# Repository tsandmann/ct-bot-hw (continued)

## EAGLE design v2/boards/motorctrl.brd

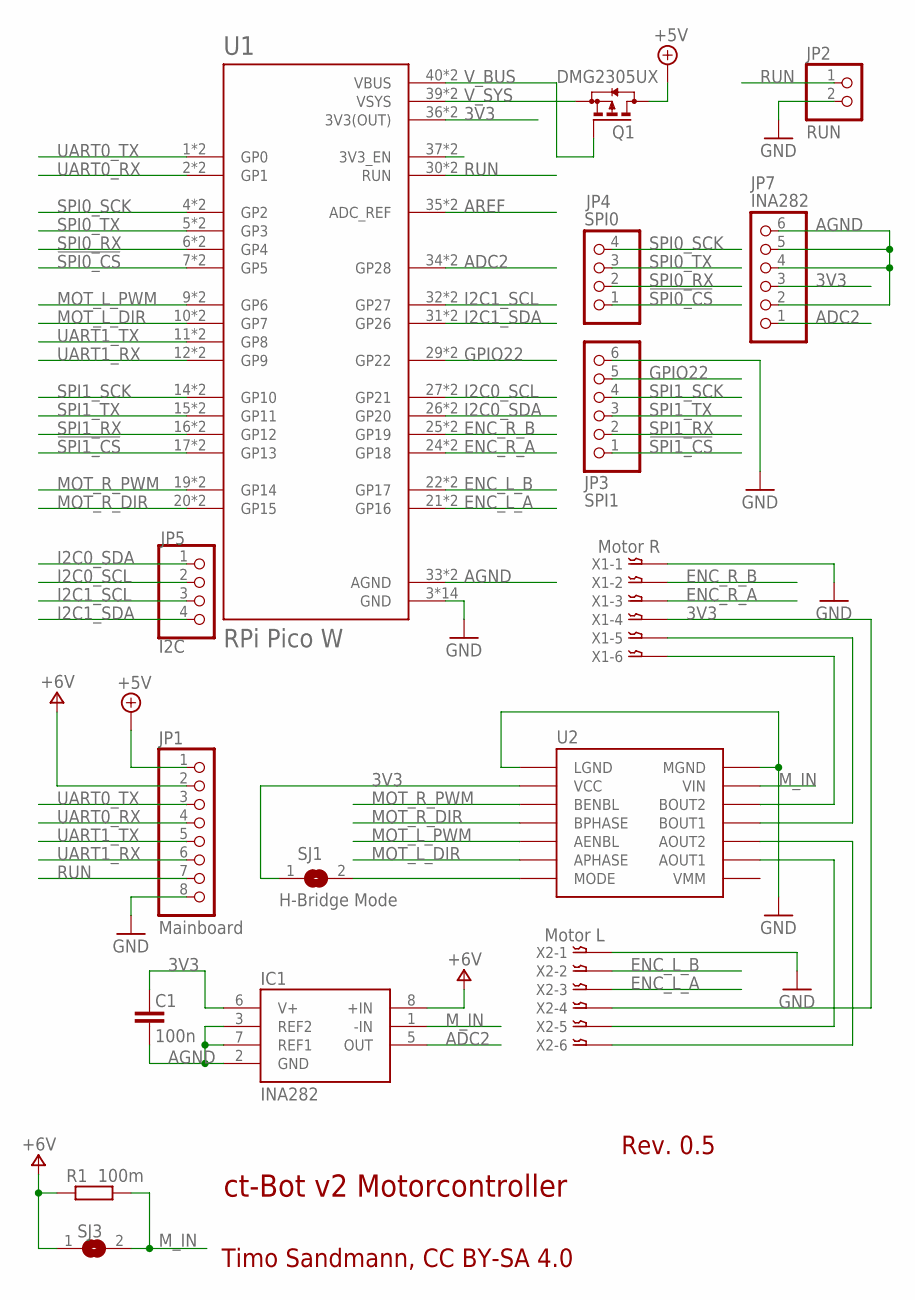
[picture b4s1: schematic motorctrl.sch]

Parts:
C1: 100n; C0805
IC1: INA282; SO08
JP1: Mainboard; 1X08
JP2: RUN; 1X02
JP3: SPI1; 1X06
JP4: SPI0; 1X04
JP5: I2C; 1X04
JP7: INA282; 1X06
Q1: DMG2305UX; SOT23
R1: 100m; R2512
SJ1: H-Bridge Mode; SJ
SJ3: VREF; SJ
U1: RPi Pico W; PICO-PKG-NO_DEBUG
U2: DRV8835THROUGHHOLE; DRV8835
X1: Motor R; B6B-XH
X2: Motor L; B6B-XH

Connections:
3V3: C1.2, IC1.6 (V+), JP7.3, SJ1.1, U1.36 (3V3(OUT)), U1.P$36 (3V3(OUT)), U2.VCC, X1.P$4, X2.P$4
3V3_EN: U1.37 (3V3_EN), U1.P$37 (3V3_EN)
!SPI0_CS: JP4.1, U1.7 (GP5), U1.P$7 (GP5)
!SPI1_CS: JP3.1, U1.17 (GP13), U1.P$17 (GP13)
+5V: JP1.1, Q1.3 (D)
+6V: IC1.8 (+IN), JP1.2, R1.1, SJ3.1
ADC2: IC1.5 (OUT), JP7.1, U1.34 (GP28), U1.P$34 (GP28)
AGND: C1.1, IC1.2 (GND), IC1.3 (REF2), IC1.7 (REF1), JP7.2, JP7.4, JP7.5, JP7.6, U1.33 (AGND), U1.P$33 (AGND)
AREF: U1.35 (ADC_REF), U1.P$35 (ADC_REF)
ENC_L_A: U1.21 (GP16), U1.P$21 (GP16), X2.P$3
ENC_L_B: U1.22 (GP17), U1.P$22 (GP17), X2.P$2
ENC_R_A: U1.24 (GP18), U1.P$24 (GP18), X1.P$3
ENC_R_B: U1.25 (GP19), U1.P$25 (GP19), X1.P$2
GND: JP1.8, JP2.2, JP3.6, U1.3 (GND), U1.8 (GND), U1.13 (GND), U1.18 (GND), U1.23 (GND), U1.28 (GND), U1.38 (GND), U1.P$3 (GND), U1.P$8 (GND), U1.P$13 (GND), U1.P$18 (GND), U1.P$23 (GND), U1.P$28 (GND), U1.P$38 (GND), U2.LGND, U2.MGND, X1.P$1, X2.P$1
GPIO22: JP3.5, U1.29 (GP22), U1.P$29 (GP22)
I2C0_SCL: JP5.2, U1.27 (GP21), U1.P$27 (GP21)
I2C0_SDA: JP5.1, U1.26 (GP20), U1.P$26 (GP20)
I2C1_SCL: JP5.3, U1.32 (GP27), U1.P$32 (GP27)
I2C1_SDA: JP5.4, U1.31 (GP26), U1.P$31 (GP26)
MOT_L_DIR: U1.10 (GP7), U1.P$10 (GP7), U2.APHASE
MOT_L_PWM: U1.9 (GP6), U1.P$9 (GP6), U2.AENBL
MOT_R_DIR: U1.20 (GP15), U1.P$20 (GP15), U2.BPHASE
MOT_R_PWM: U1.19 (GP14), U1.P$19 (GP14), U2.BENBL
M_IN: IC1.1 (-IN), R1.2, SJ3.2, U2.VIN
unnamed: SJ1.2, U2.MODE
unnamed: U2.BOUT1, X1.P$5
unnamed: U2.BOUT2, X1.P$6
unnamed: U2.AOUT1, X2.P$5
unnamed: U2.AOUT2, X2.P$6
RUN: JP1.7, JP2.1, U1.30 (RUN), U1.P$30 (RUN)
SPI0_RX: JP4.2, U1.6 (GP4), U1.P$6 (GP4)
SPI0_SCK: JP4.4, U1.4 (GP2), U1.P$4 (GP2)
SPI0_TX: JP4.3, U1.5 (GP3), U1.P$5 (GP3)
SPI1_RX: JP3.2, U1.16 (GP12), U1.P$16 (GP12)
SPI1_SCK: JP3.4, U1.14 (GP10), U1.P$14 (GP10)
SPI1_TX: JP3.3, U1.15 (GP11), U1.P$15 (GP11)
UART0_RX: JP1.4, U1.2 (GP1), U1.P$2 (GP1)
UART0_TX: JP1.3, U1.1 (GP0), U1.P$1 (GP0)
UART1_RX: JP1.6, U1.12 (GP9), U1.P$12 (GP9)
UART1_TX: JP1.5, U1.11 (GP8), U1.P$11 (GP8)
V_BUS: Q1.1 (G), U1.40 (VBUS), U1.P$40 (VBUS)
V_SYS: Q1.2 (S), U1.39 (VSYS), U1.P$39 (VSYS)

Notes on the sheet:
Rev. 0.5
Timo Sandmann, CC BY-SA 4.0
ct-Bot v2 Motorcontroller

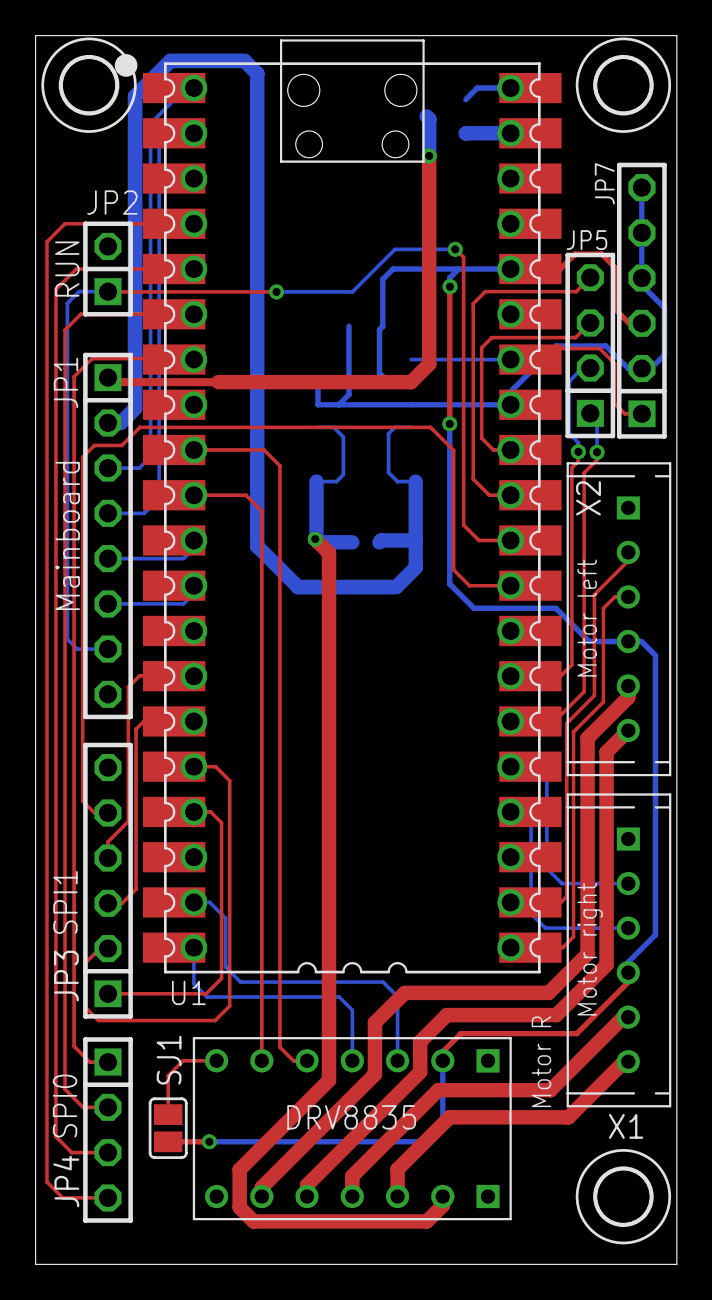
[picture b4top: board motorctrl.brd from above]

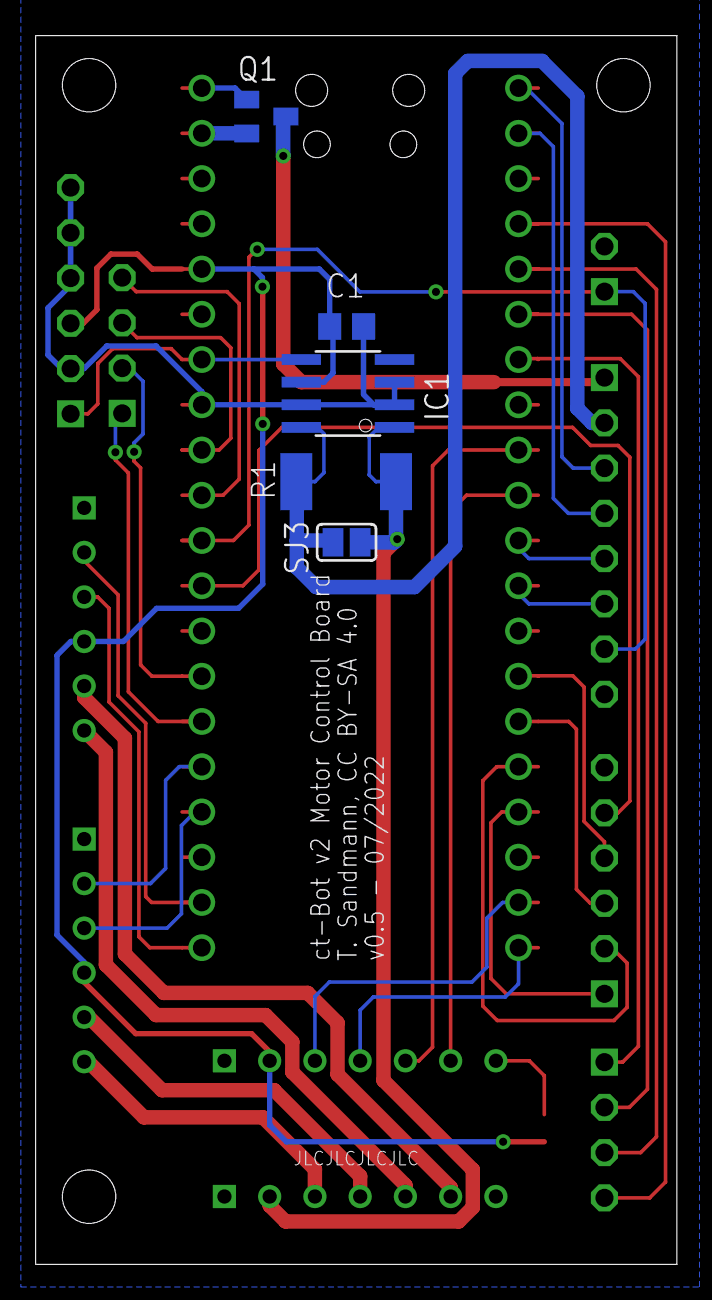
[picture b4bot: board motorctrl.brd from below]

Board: 2 copper layers, 36.0 x 69.0 mm, 19 parts (5 on the bottom side), 42 nets.

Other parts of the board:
H1, H2, H3: MOUNT-HOLE3.0; 3,0

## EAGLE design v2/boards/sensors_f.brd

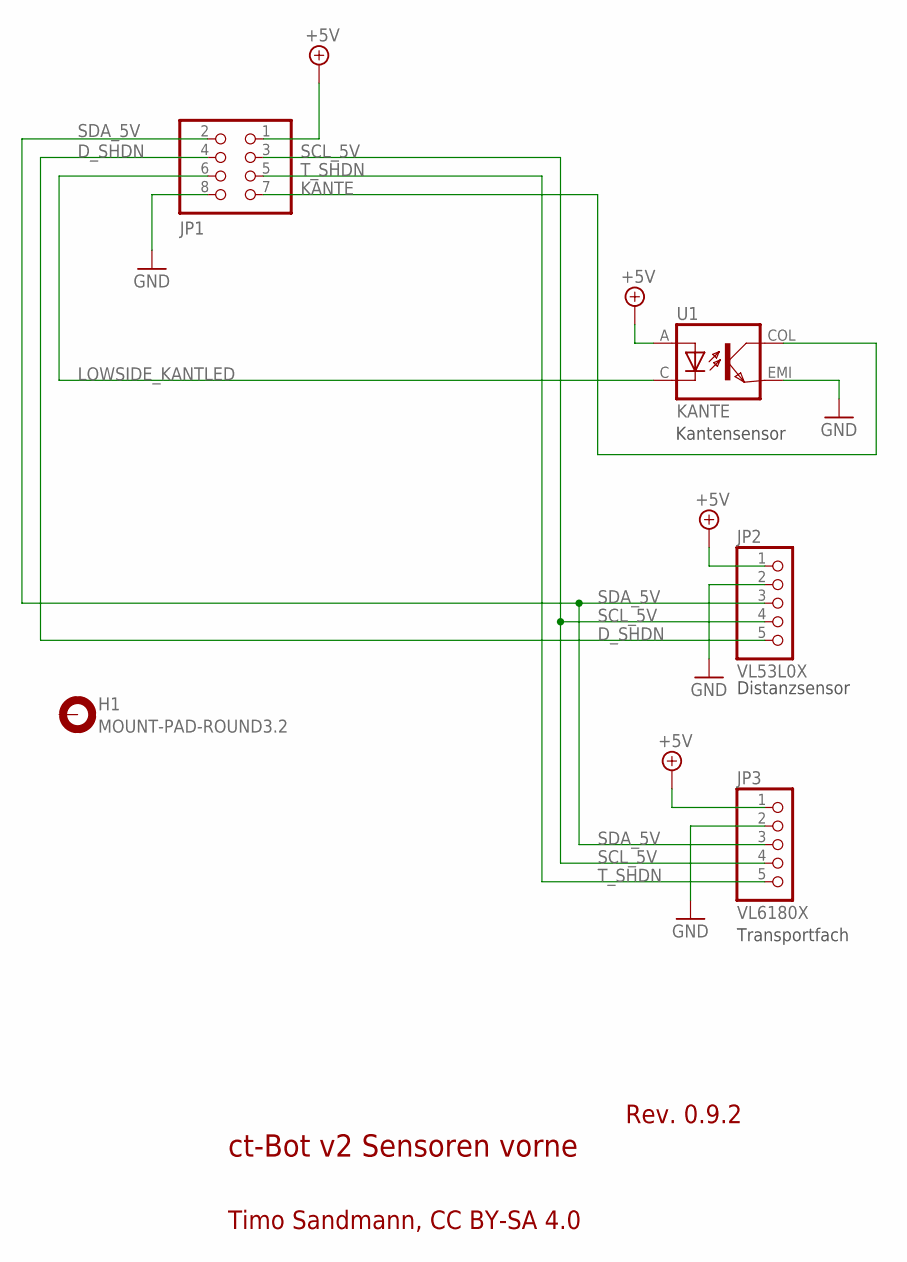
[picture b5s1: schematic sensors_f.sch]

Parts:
H1: MOUNT-PAD-ROUND3.2; 3,2-PAD
JP1: PINHD-2X4; 2X04
JP2: VL53L0X; 1X05
JP3: VL6180X; 1X05
U1: KANTE; EDGE

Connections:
+5V: JP1.1, JP2.1, JP3.1, U1.A
D_SHDN: JP1.4, JP2.5
GND: JP1.8, JP2.2, JP3.2, U1.EMI
KANTE: JP1.7, U1.COL
LOWSIDE_KANTLED: JP1.6, U1.C
SCL_5V: JP1.3, JP2.4, JP3.4
SDA_5V: JP1.2, JP2.3, JP3.3
T_SHDN: JP1.5, JP3.5

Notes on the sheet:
ct-Bot v2 Sensoren vorne
Rev. 0.9.2
Timo Sandmann, CC BY-SA 4.0
Kantensensor
Distanzsensor
Transportfach

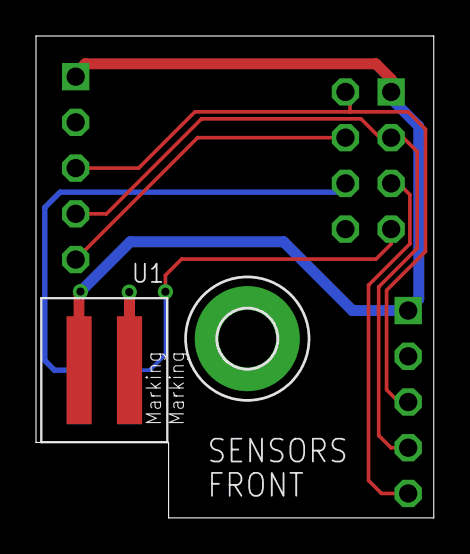
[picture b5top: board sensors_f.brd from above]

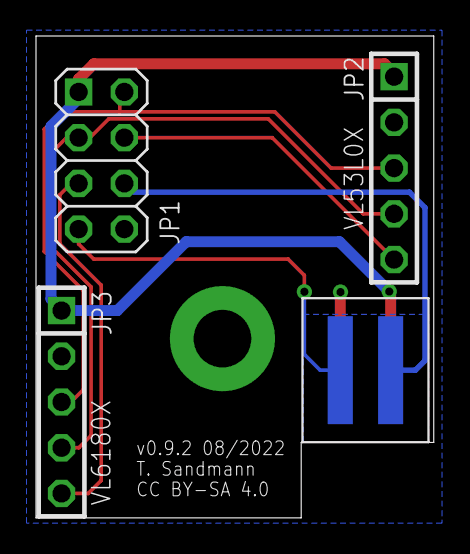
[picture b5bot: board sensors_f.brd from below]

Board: 2 copper layers, 22.1 x 26.8 mm, 5 parts (3 on the bottom side), 8 nets.

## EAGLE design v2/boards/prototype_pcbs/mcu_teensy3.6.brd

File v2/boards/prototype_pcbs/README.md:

# ct-Bot v2 prototype test boards

These boards (a simplified mainboard, a teensy mcu board, and three sensor boards) are ***prototypes*** just for ***development and testing***. They are provided "as is" without warranty of any kind.

## Simplified mainboard

To achieve a more cost-effective prototype board with only two layers, some optional extensions have been omitted, and the various I2C buses have been combined. See [mainboard_2l_0.8.3.pdf](mainboard_2l_0.8.3.pdf) for the simplified schematic. However, the basic functionality has been successfully tested. See [known issues](#Known-issues-and-notes) for problems discovered so far.

## Known issues and notes

Please note: these problem lists may be highly incomplete, as not all functions have been tested yet!

### [Mainboard](mainboard_2l_0.8.3.pdf)

* *I2C0* Pullups may be incorrect, depending on the connected modules, line capacities are not considered.
* A pullup is missing on ESP32's RX line.
* Reset buttons for MCU and ESP32 are missing.
* Analog signal paths are noisy due to simplified 2-layer design.
* There may be crosstalk due to the simplified 2-layer design.
* The BNO055 sensor connector should be extended by another one for an MPU 6050 sensor (as a better alternative).

### [Teensy MCU board](mcu_teensy_0.8.4.pdf)

* 3V3 reference voltage should be added to increase accurancy and stability of ADC.
* *I2C0_5V* is not necessary.
* *U2* and *Q1* are not necessary.
* RTC bat is not necessary.

### [Line sensor board (bottom)](sensors_b_0.8.4.pdf)

* Signals for left and right line sensors are swapped. Workaround: exchange *LINE_L* and *LINE_R* on mainboard connector or swap pin mappings in software.

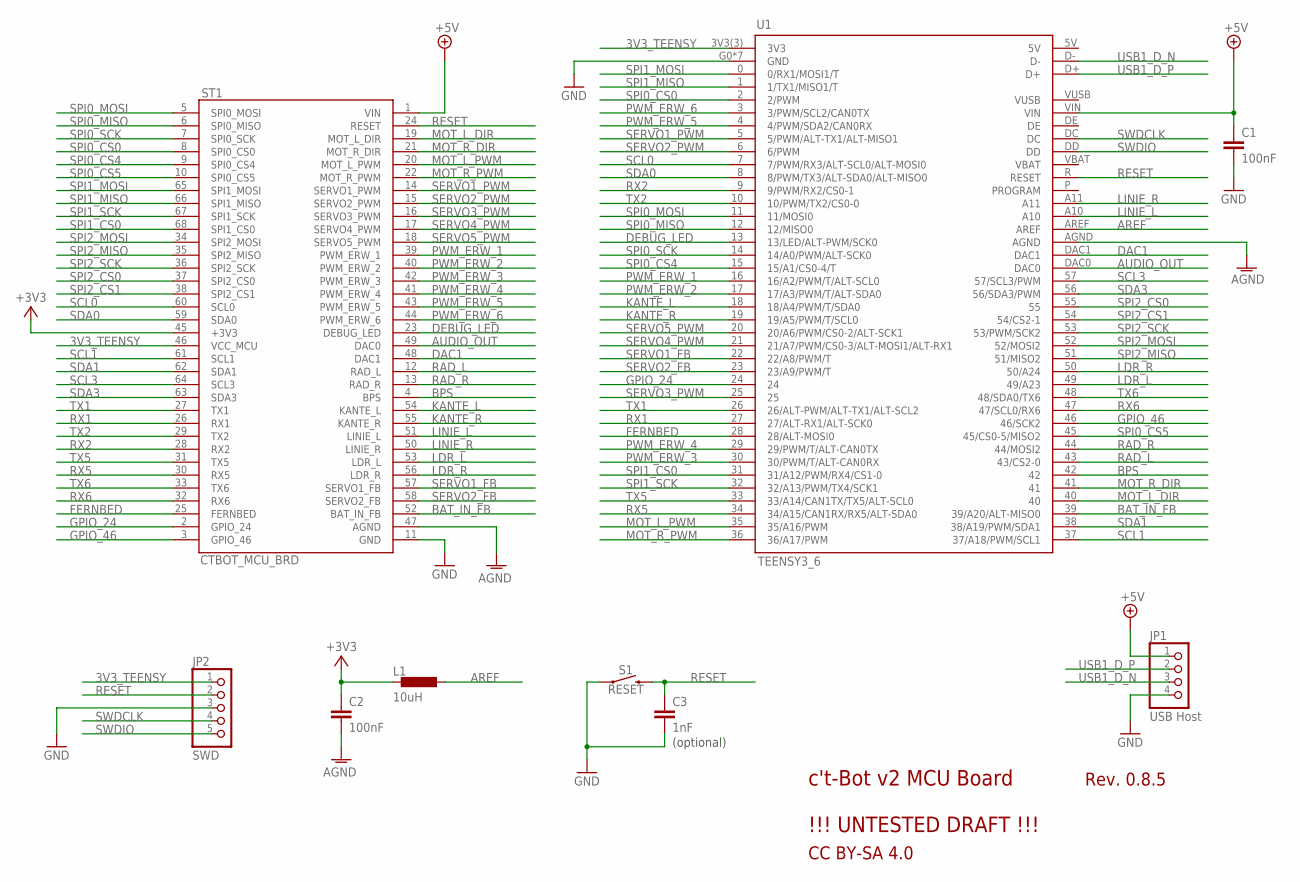
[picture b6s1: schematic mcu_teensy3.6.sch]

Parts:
C1, C2: 100nF; C025-025X050
C3: 1nF; C025-025X050
JP1: USB Host; 1X04/90
JP2: SWD; 1X05/90
L1: 10uH; 0207/10
S1: RESET; TACTILE_SWITCH_PTH_6.0MM
ST1: CTBOT_MCU_BRD; DIP66
U1: TEENSY3_6; T36

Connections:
3V3_TEENSY: JP2.1, ST1.46 (VCC_MCU), U1.3V3(3) (3V3)
+3V3: C2.1, L1.2, ST1.45 (+3V3)
+5V: C1.1, JP1.1, ST1.1 (VIN), U1.VIN
AGND: C2.2, ST1.47 (AGND), U1.AGND
AREF: L1.1, U1.AREF
AUDIO_OUT: ST1.49 (DAC0), U1.DAC0
BAT_IN_FB: ST1.52 (BAT_IN_FB), U1.39 (39/A20/ALT-MISO0)
BPS: ST1.4 (BPS), U1.42
DAC1: ST1.48 (DAC1), U1.DAC1
DEBUG_LED: ST1.23 (DEBUG_LED), U1.13 (13/LED/ALT-PWM/SCK0)
FERNBED: ST1.25 (FERNBED), U1.28 (28/ALT-MOSI0)
GND: C1.2, C3.2, JP1.4, JP2.3, S1.1, ST1.11 (GND), U1.G0 (GND), U1.G1 (GND), U1.G2 (GND), U1.G3 (GND), U1.G4 (GND), U1.G5 (GND), U1.G6 (GND)
GPIO_24: ST1.2 (GPIO_24), U1.24
GPIO_46: ST1.3 (GPIO_46), U1.46 (46/SCK2)
KANTE_L: ST1.54 (KANTE_L), U1.18 (18/A4/PWM/T/SDA0)
KANTE_R: ST1.55 (KANTE_R), U1.19 (19/A5/PWM/T/SCL0)
LDR_L: ST1.53 (LDR_L), U1.49 (49/A23)
LDR_R: ST1.56 (LDR_R), U1.50 (50/A24)
LINIE_L: ST1.51 (LINIE_L), U1.A10
LINIE_R: ST1.50 (LINIE_R), U1.A11
MOT_L_DIR: ST1.19 (MOT_L_DIR), U1.40
MOT_L_PWM: ST1.20 (MOT_L_PWM), U1.35 (35/A16/PWM)
MOT_R_DIR: ST1.21 (MOT_R_DIR), U1.41
MOT_R_PWM: ST1.22 (MOT_R_PWM), U1.36 (36/A17/PWM)
PWM_ERW_1: ST1.39 (PWM_ERW_1), U1.16 (16/A2/PWM/T/ALT-SCL0)
PWM_ERW_2: ST1.40 (PWM_ERW_2), U1.17 (17/A3/PWM/T/ALT-SDA0)
PWM_ERW_3: ST1.42 (PWM_ERW_3), U1.30 (30/PWM/T/ALT-CAN0RX)
PWM_ERW_4: ST1.41 (PWM_ERW_4), U1.29 (29/PWM/T/ALT-CAN0TX)
PWM_ERW_5: ST1.43 (PWM_ERW_5), U1.4 (4/PWM/SDA2/CAN0RX)
PWM_ERW_6: ST1.44 (PWM_ERW_6), U1.3 (3/PWM/SCL2/CAN0TX)
RAD_L: ST1.12 (RAD_L), U1.43 (43/CS2-0)
RAD_R: ST1.13 (RAD_R), U1.44 (44/MOSI2)
RESET: C3.1, JP2.2, S1.3 (2), ST1.24 (RESET), U1.R (RESET)
RX1: ST1.26 (RX1), U1.27 (27/ALT-RX1/ALT-SCK0)
RX2: ST1.28 (RX2), U1.9 (9/PWM/RX2/CS0-1)
RX5: ST1.30 (RX5), U1.34 (34/A15/CAN1RX/RX5/ALT-SDA0)
RX6: ST1.32 (RX6), U1.47 (47/SCL0/RX6)
SCL0: ST1.60 (SCL0), U1.7 (7/PWM/RX3/ALT-SCL0/ALT-MOSI0)
SCL1: ST1.61 (SCL1), U1.37 (37/A18/PWM/SCL1)
SCL3: ST1.64 (SCL3), U1.57 (57/SCL3/PWM)
SDA0: ST1.59 (SDA0), U1.8 (8/PWM/TX3/ALT-SDA0/ALT-MISO0)
SDA1: ST1.62 (SDA1), U1.38 (38/A19/PWM/SDA1)
SDA3: ST1.63 (SDA3), U1.56 (56/SDA3/PWM)
SERVO1_FB: ST1.57 (SERVO1_FB), U1.22 (22/A8/PWM/T)
SERVO1_PWM: ST1.14 (SERVO1_PWM), U1.5 (5/PWM/ALT-TX1/ALT-MISO1)
SERVO2_FB: ST1.58 (SERVO2_FB), U1.23 (23/A9/PWM/T)
SERVO2_PWM: ST1.15 (SERVO2_PWM), U1.6 (6/PWM)
SERVO3_PWM: ST1.16 (SERVO3_PWM), U1.25
SERVO4_PWM: ST1.17 (SERVO4_PWM), U1.21 (21/A7/PWM/CS0-3/ALT-MOSI1/ALT-RX1)
SERVO5_PWM: ST1.18 (SERVO5_PWM), U1.20 (20/A6/PWM/CS0-2/ALT-SCK1)
SPI0_CS0: ST1.8 (SPI0_CS0), U1.2 (2/PWM)
SPI0_CS4: ST1.9 (SPI0_CS4), U1.15 (15/A1/CS0-4/T)
SPI0_CS5: ST1.10 (SPI0_CS5), U1.45 (45/CS0-5/MISO2)
SPI0_MISO: ST1.6 (SPI0_MISO), U1.12 (12/MISO0)
SPI0_MOSI: ST1.5 (SPI0_MOSI), U1.11 (11/MOSI0)
SPI0_SCK: ST1.7 (SPI0_SCK), U1.14 (14/A0/PWM/ALT-SCK0)
SPI1_CS0: ST1.68 (SPI1_CS0), U1.31 (31/A12/PWM/RX4/CS1-0)
SPI1_MISO: ST1.66 (SPI1_MISO), U1.1 (1/TX1/MISO1/T)
SPI1_MOSI: ST1.65 (SPI1_MOSI), U1.0 (0/RX1/MOSI1/T)
SPI1_SCK: ST1.67 (SPI1_SCK), U1.32 (32/A13/PWM/TX4/SCK1)
SPI2_CS0: ST1.37 (SPI2_CS0), U1.55
SPI2_CS1: ST1.38 (SPI2_CS1), U1.54 (54/CS2-1)
SPI2_MISO: ST1.35 (SPI2_MISO), U1.51 (51/MISO2)
SPI2_MOSI: ST1.34 (SPI2_MOSI), U1.52 (52/MOSI2)
SPI2_SCK: ST1.36 (SPI2_SCK), U1.53 (53/PWM/SCK2)
SWDCLK: JP2.4, U1.DC
SWDIO: JP2.5, U1.DD
TX1: ST1.27 (TX1), U1.26 (26/ALT-PWM/ALT-TX1/ALT-SCL2)
TX2: ST1.29 (TX2), U1.10 (10/PWM/TX2/CS0-0)
TX5: ST1.31 (TX5), U1.33 (33/A14/CAN1TX/TX5/ALT-SCL0)
TX6: ST1.33 (TX6), U1.48 (48/SDA0/TX6)
USB1_D_N: JP1.3, U1.D-
USB1_D_P: JP1.2, U1.D+

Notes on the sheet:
c't-Bot v2 MCU Board !!! UNTESTED DRAFT !!!
Rev. 0.8.5
CC BY-SA 4.0
(optional)

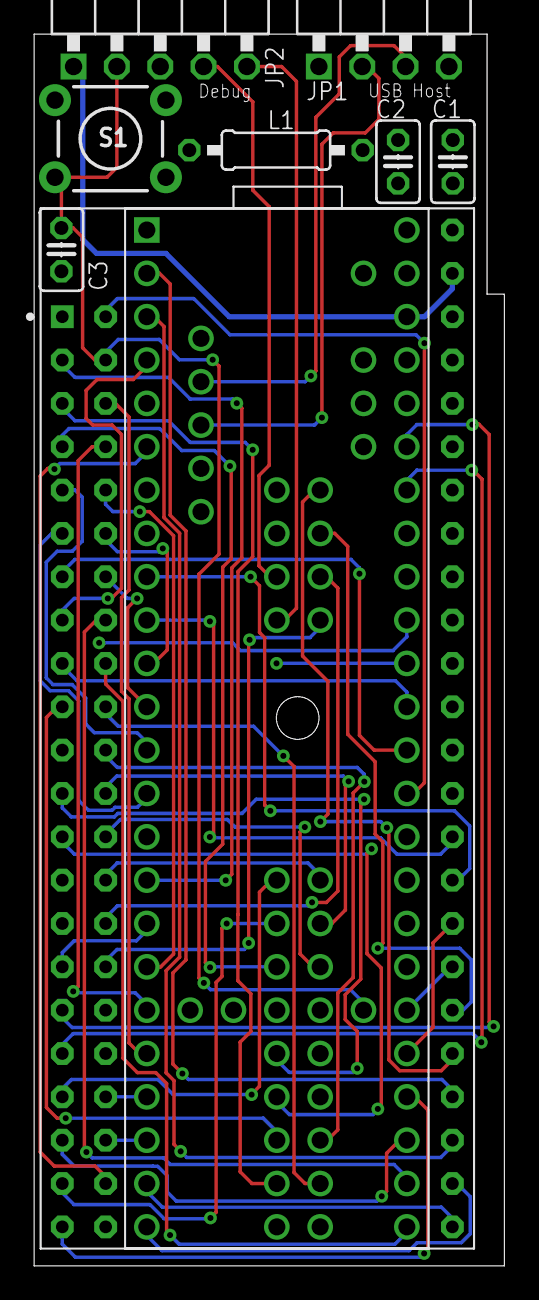
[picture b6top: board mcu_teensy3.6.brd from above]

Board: 4 copper layers, 27.6 x 72.2 mm, 9 parts (0 on the bottom side), 73 nets.

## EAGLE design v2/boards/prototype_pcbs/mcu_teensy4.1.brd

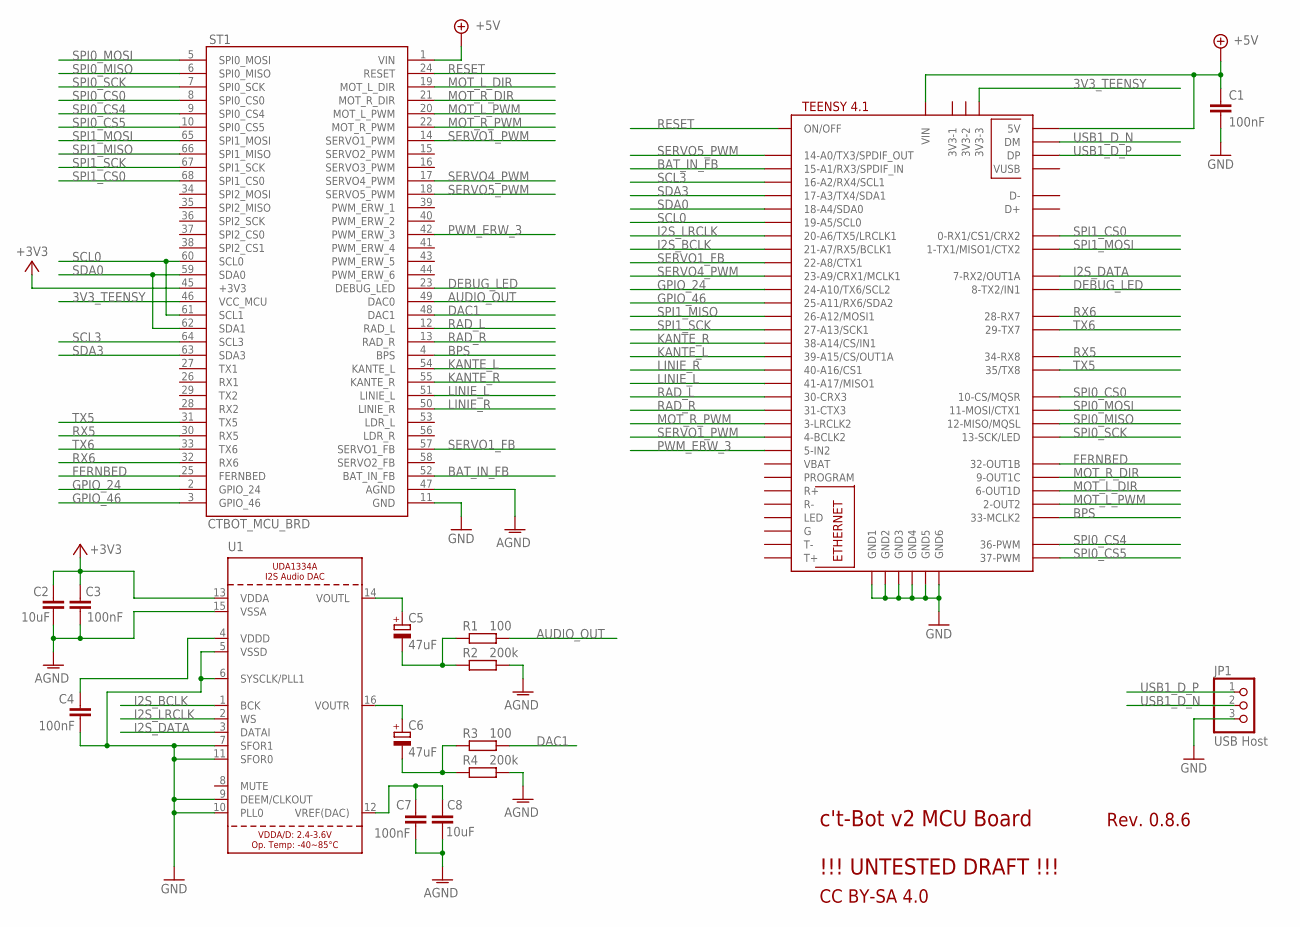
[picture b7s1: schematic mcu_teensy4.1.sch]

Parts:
C1, C3, C4, C7: 100nF; C0805
C2, C8: 10uF; C0805
C5, C6: 47uF; UD-6,3X5,8_NICHICON
JP1: USB Host; 1X03/90
R1, R3: 100; R0805
R2, R4: 200k; R0805
ST1: CTBOT_MCU_BRD; DIP66
U1: AUDIO_I2S_UDA1334""; SSOP16_4.4MM
U$1: TEENSY41

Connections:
3V3_TEENSY: ST1.46 (VCC_MCU), U$1.3V3-3
+3V3: C2.1, C3.2, ST1.45 (+3V3), U1.13 (VDDA)
+5V: C1.1, ST1.1 (VIN), U$1.+5V (5V), U$1.VIN
AGND: C2.2, C3.1, C7.1, C8.1, R2.2, R4.2, ST1.47 (AGND), U1.15 (VSSA)
AUDIO_OUT: R1.2, ST1.49 (DAC0)
BAT_IN_FB: ST1.52 (BAT_IN_FB), U$1.15-A1/RX3/SPDIF_IN
BPS: ST1.4 (BPS), U$1.33-MCLK2
DAC1: R3.2, ST1.48 (DAC1)
DEBUG_LED: ST1.23 (DEBUG_LED), U$1.8-TX2/IN1
FERNBED: ST1.25 (FERNBED), U$1.32-OUT1B
GND: C1.2, C4.1, JP1.3, ST1.11 (GND), U1.5 (VSSD), U1.6 (SYSCLK/PLL1), U1.7 (SFOR1), U1.9 (DEEM/CLKOUT), U1.10 (PLL0), U1.11 (SFOR0), U$1.GND1, U$1.GND2, U$1.GND3, U$1.GND4, U$1.GND5, U$1.GND6
GPIO_24: ST1.2 (GPIO_24), U$1.24-A10/TX6/SCL2
GPIO_46: ST1.3 (GPIO_46), U$1.25-A11/RX6/SDA2
I2S_BCLK: U1.1 (BCK), U$1.21-A7/RX5/BCLK1
I2S_DATA: U1.3 (DATAI), U$1.7-RX2/OUT1A
I2S_LRCLK: U1.2 (WS), U$1.20-A6/TX5/LRCLK1
KANTE_L: ST1.54 (KANTE_L), U$1.39-A15/CS/OUT1A
KANTE_R: ST1.55 (KANTE_R), U$1.38-A14/CS/IN1
LINIE_L: ST1.51 (LINIE_L), U$1.41-A17/MISO1
LINIE_R: ST1.50 (LINIE_R), U$1.40-A16/CS1
MOT_L_DIR: ST1.19 (MOT_L_DIR), U$1.6-OUT1D
MOT_L_PWM: ST1.20 (MOT_L_PWM), U$1.2-OUT2
MOT_R_DIR: ST1.21 (MOT_R_DIR), U$1.9-OUT1C
MOT_R_PWM: ST1.22 (MOT_R_PWM), U$1.3-LRCLK2
unnamed: C7.2, C8.2, U1.12 (VREF(DAC))
unnamed: C5.+, U1.14 (VOUTL)
unnamed: C4.2, U1.4 (VDDD)
unnamed: C6.+, U1.16 (VOUTR)
unnamed: C5.-, R1.1, R2.1
unnamed: C6.-, R3.1, R4.1
PWM_ERW_3: ST1.42 (PWM_ERW_3), U$1.5-IN2
RAD_L: ST1.12 (RAD_L), U$1.30-CRX3
RAD_R: ST1.13 (RAD_R), U$1.31-CTX3
RESET: ST1.24 (RESET), U$1.ON/OFF
RX5: ST1.30 (RX5), U$1.34-RX8
RX6: ST1.32 (RX6), U$1.28-RX7
SCL0: ST1.60 (SCL0), ST1.61 (SCL1), U$1.19-A5/SCL0
SCL3: ST1.64 (SCL3), U$1.16-A2/RX4/SCL1
SDA0: ST1.59 (SDA0), ST1.62 (SDA1), U$1.18-A4/SDA0
SDA3: ST1.63 (SDA3), U$1.17-A3/TX4/SDA1
SERVO1_FB: ST1.57 (SERVO1_FB), U$1.22-A8/CTX1
SERVO1_PWM: ST1.14 (SERVO1_PWM), U$1.4-BCLK2
SERVO4_PWM: ST1.17 (SERVO4_PWM), U$1.23-A9/CRX1/MCLK1
SERVO5_PWM: ST1.18 (SERVO5_PWM), U$1.14-A0/TX3/SPDIF_OUT
SPI0_CS0: ST1.8 (SPI0_CS0), U$1.10-CS\MQSR (10-CS/MQSR)
SPI0_CS4: ST1.9 (SPI0_CS4), U$1.36-PWM
SPI0_CS5: ST1.10 (SPI0_CS5), U$1.37-PWM
SPI0_MISO: ST1.6 (SPI0_MISO), U$1.12-MISO/MQSL
SPI0_MOSI: ST1.5 (SPI0_MOSI), U$1.11-MOSI/CTX1
SPI0_SCK: ST1.7 (SPI0_SCK), U$1.13-SCK/LED
SPI1_CS0: ST1.68 (SPI1_CS0), U$1.0-RX1/CS1/CRX2
SPI1_MISO: ST1.66 (SPI1_MISO), U$1.26-A12/MOSI1
SPI1_MOSI: ST1.65 (SPI1_MOSI), U$1.1-TX1/MISO1/CTX2
SPI1_SCK: ST1.67 (SPI1_SCK), U$1.27-A13/SCK1
TX5: ST1.31 (TX5), U$1.35-TX8 (35/TX8)
TX6: ST1.33 (TX6), U$1.29-TX7
USB1_D_N: JP1.2, U$1.DM
USB1_D_P: JP1.1, U$1.DP

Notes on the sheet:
c't-Bot v2 MCU Board !!! UNTESTED DRAFT !!!
Rev. 0.8.6
CC BY-SA 4.0

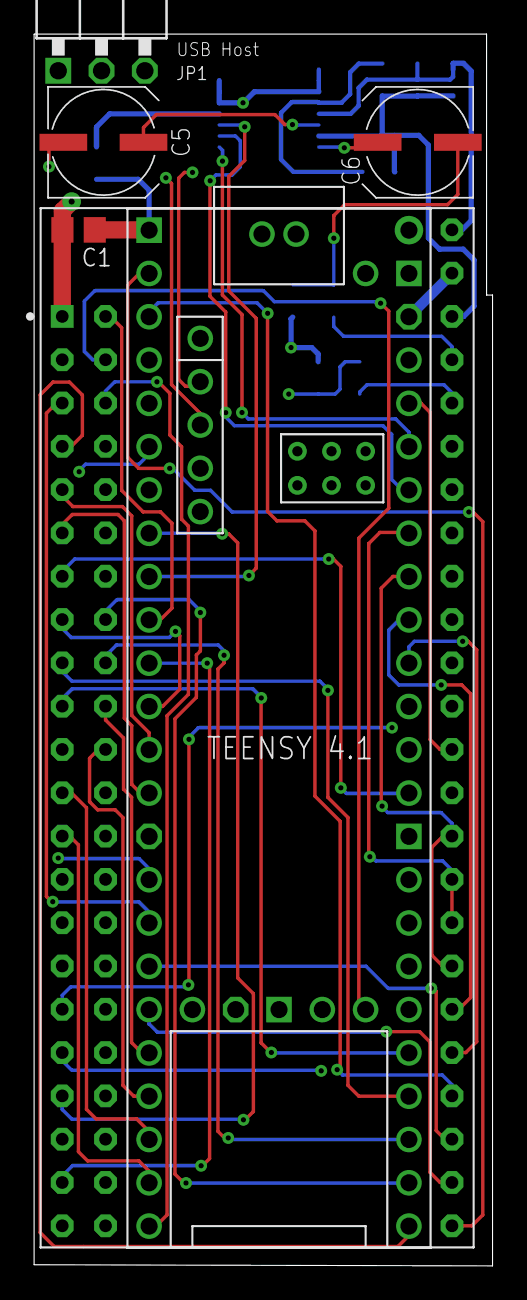
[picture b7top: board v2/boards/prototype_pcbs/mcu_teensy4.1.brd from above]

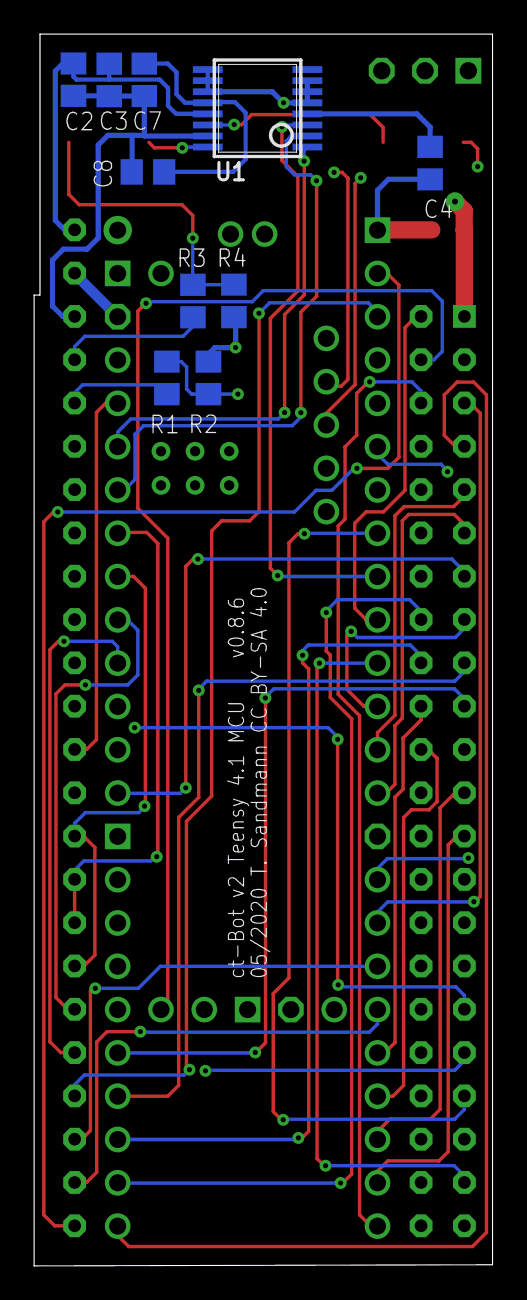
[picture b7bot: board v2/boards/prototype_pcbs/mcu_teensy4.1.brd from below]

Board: 4 copper layers, 26.9 x 72.3 mm, 16 parts (10 on the bottom side), 58 nets.

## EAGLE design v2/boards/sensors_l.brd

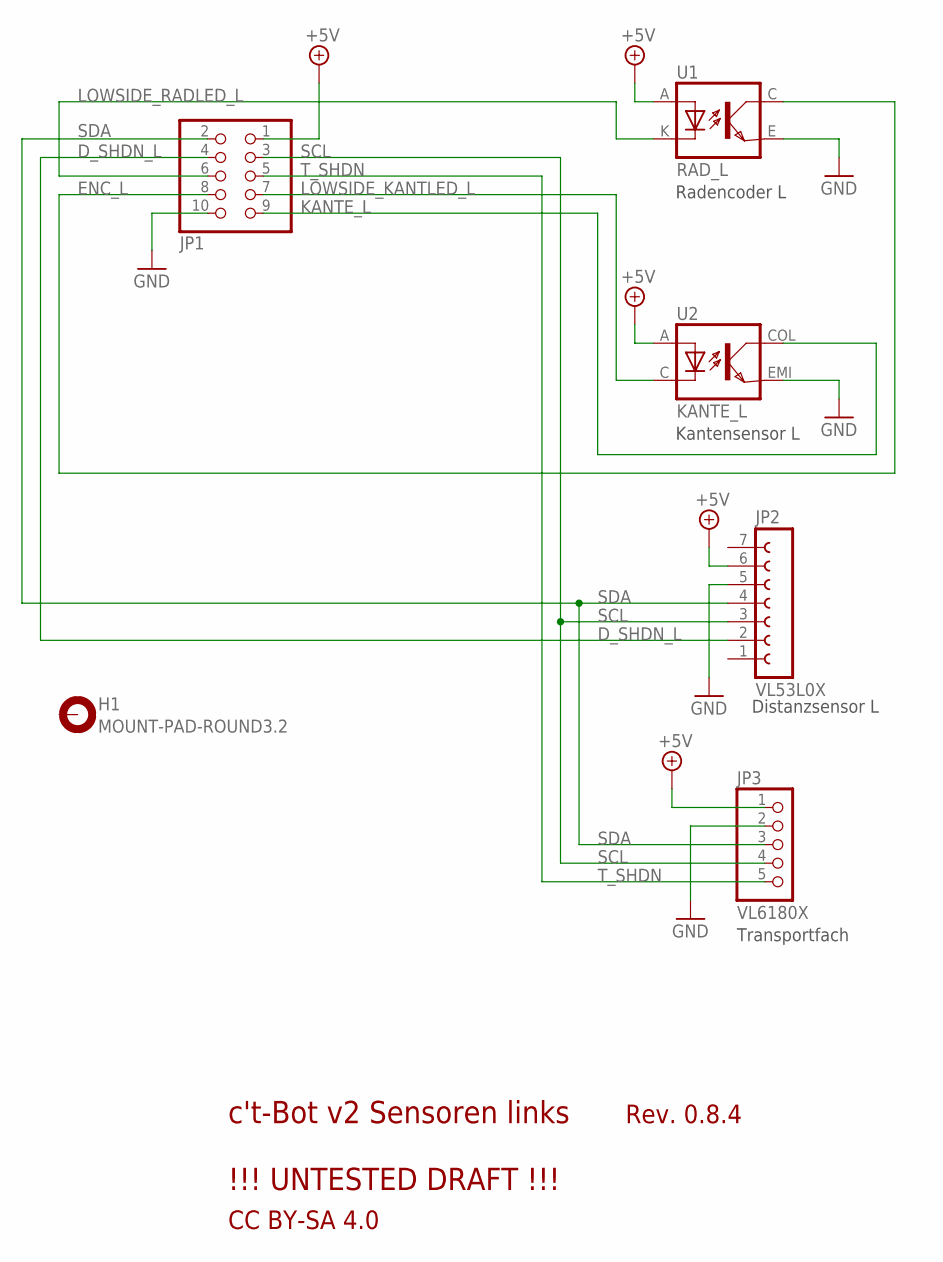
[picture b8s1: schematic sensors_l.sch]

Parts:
H1: MOUNT-PAD-ROUND3.2; 3,2-PAD
JP1: PINHD-2X5; 2X05
JP2: VL53L0X; FE07W
JP3: VL6180X; 1X05
U1: RAD_L; 4
U2: KANTE_L; EDGE

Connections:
+5V: JP1.1, JP2.6, JP3.1, U1.A, U2.A
D_SHDN_L: JP1.4, JP2.2
ENC_L: JP1.8, U1.C (COL)
GND: JP1.10, JP2.5, JP3.2, U1.E (EMI), U2.EMI
KANTE_L: JP1.9, U2.COL
LOWSIDE_KANTLED_L: JP1.7, U2.C
LOWSIDE_RADLED_L: JP1.6, U1.K (C)
SCL: JP1.3, JP2.3, JP3.4
SDA: JP1.2, JP2.4, JP3.3
T_SHDN: JP1.5, JP3.5

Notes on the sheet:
c't-Bot v2 Sensoren links !!! UNTESTED DRAFT !!!
Rev. 0.8.4
CC BY-SA 4.0
Radencoder L
Kantensensor L
Distanzsensor L
Transportfach

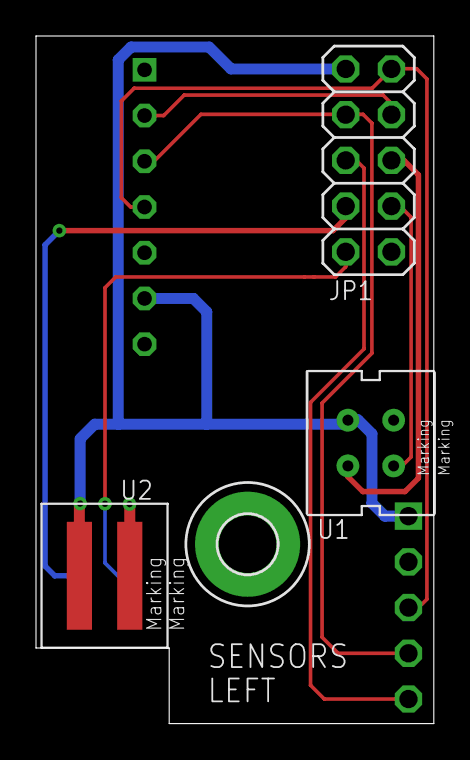
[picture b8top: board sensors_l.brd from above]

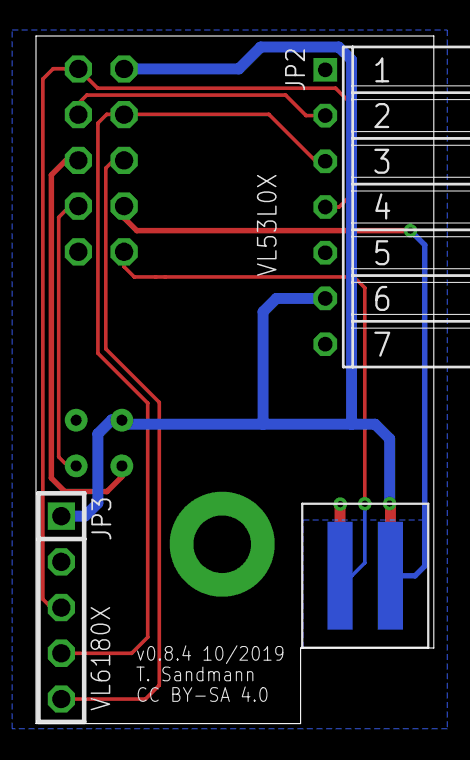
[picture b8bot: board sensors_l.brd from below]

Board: 2 copper layers, 22.1 x 38.2 mm, 6 parts (2 on the bottom side), 10 nets.

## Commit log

2018-03-03 Initial commit of ct-Bot v2 schematic and pin mapping drafts
2018-03-03 license file added
2018-03-03 baseplate dimensions and v1 schematics added
2018-03-04 Servo PWM pullups corrected, battery voltage divider adjusted
    schematic layout improved, signal names unified
2018-03-19 Added current datasheets for components used in schematics (Rev. 0.2).
2018-03-19 bugfix for i2c bus mapping on mainboard
2018-03-19 Removed .project settings file from git file index.
2018-03-19 Removed old .project settings file.
2018-03-20 Added datasheet for BNO055 sensor.
2018-03-21 Added datasheet for SG92R servo.
2018-03-22 Added datasheet for SG90 servo.
2018-03-24 schematics updated to rev 0.3
2018-03-26 Added datasheet for LCD Display.
2018-03-26 mainboard: signal names updated
2018-03-29 datasheets added / updated
2018-03-29 New folder structure for project.
2018-03-29 Completed new folder structure. Sorted files (Part 1).
2018-03-29 Updated datasheets to latest revisions. Cleanup.
2018-03-29 Added datasheets for ct-Bot (v1). New folder structure (Part 2).
2018-03-29 Added pcb-layouts and further schematics for ct-Bot (v1).
2018-03-29 Added old articles from ct-magazine [(c) heise].
2018-03-29 Improved folder structure.
2018-03-29 teensy pin mapping as ods file added
2018-03-30 cleanup
2018-04-03 two small adapter boards (just for development / testing) added: for motor driver and teensy
2018-04-03 Datasheets: ATmega MCs, ISP mkII Programmer & TXB0104 Level Converter.
2018-04-08 Added datasheet for MCU ATmega 664.
2018-05-21 bugfixes for wrong voltage dividers
2018-07-25 produced prototype version of adapter board
2018-10-07 teensy adapter board updated to version 2 with…
    - bugfixes
    - reset controller
    - audio
    - swd debugger port
2018-10-13 teensy adapter board v2 updated: bugfix silkscreen
2018-10-17 teensy adapter v2: layout images after gerber processing
2019-01-13 cleanup of schematic, bugfix wheel encoder circuit
2019-04-08 bugfix teensy adapter schematic: teensy pin 49/50 naming updated
2019-04-13 Updated datasheet for MCUs ATmega 644P/1284P.
2019-04-26 teensy 3.6 pin mapping updated
    several corrections after some first tests
2019-04-27 Update for ct-bot v2 design files
    - Moved some datasheets to correct place.
    - Fix for PJRC teensy schematic.
    - Updated pin mapping table for teensy board.
    - Removed PJRC teensy pinout cards (duplicate).
2019-05-06 Moved in content from documentation repository.
    - Updated datasheets.
    - Added latest versions of original schematics.
    - Added original pcb-layouts (higher resolution).
    - Alligned naming of some files.
2019-05-13 Updated schematics to Revision 0.6.
2019-05-13 Added used EAGLE libraries (CC-BY-SA 4.0).
2019-05-19 Updated datasheets for v1.
    Some ICs remain in production as PDIP package by TI.
2019-06-01 ct-bot v2 schematic updated
    - bugfix for library references, non-managed libraries added as dedicated library (ct-bot.lbr)
    - wrong footprints reverted
    - bufix for wrong signals for servo supplies
    - bugfix reverse polarity protection
    - bugifx for line sensor voltage levels
    - small smd parts exchanged with TH alternatives (bs108, mcp101) (untested)
2019-06-01 folder structure updated for eagle design files, draft for mainboard layout added:
    - geometry based on ct-Bot dimensions
    - 1st layout for buck converters
    - very 1st draft of placement for other parts (incomplete)
2019-06-29 Added missing datasheet for hw v1.
2019-08-04 ct-bot v2 schematic updated
    - use of i2c sensors
    - adjustable luminosity for CNY70 sensors
    - ENA driver circuit updated for low-side switching
    - ESP32 for Wi-Fi, SWD, RC5 decoding
2019-08-05 PCA9672D (no longer manufactured) replaced with PCA9554D
2019-08-07 resistor values for audio amp updated
2019-08-11 ct-bot v2 schematic updated
    - optional current measurements added to mainboard
    - schematic drafts for sensor boards
    - pin mapping sheet updated (i2c-bus mapping)
2019-08-11 pin mapping sheet updated: fix for missing line
2019-08-13 Removed spaces in file names, to avoid linking problems in markdown.
2019-08-25 ct-bot v2 schematic updated according to todo list
    - analog ground
2019-08-25 ct-bot v2 schematic updated according to todo list
    - missing lib added
2019-09-21 mainboard updated:
    - some bugfixes after further testing
    - discrete MCU board added
2019-09-21 pin mapping table updated after further testing
2019-09-29 ct-Bot v2 CAD files added for 3D printing
2019-10-01 cad files: base plate updated
2019-12-22 ct-Bot v2 prototype test boards updated/added
    Simplified mainboard, teensy mcu board, and sensor boards are very early prototypes just for development and testing.
2021-09-04 cad model updates
2021-09-04 cad updates for new motors
2022-06-25 folder structure cleanup, 3d model: base updated
2023-01-01 MCU schematic and pin-mappings added
2023-01-01 CAD files updated for ct-Bot v2
2023-01-07 schematics and board files for ct-Bot v2 prototype
